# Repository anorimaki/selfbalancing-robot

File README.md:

# SelfBalancing Robot (Yes, another self balancing robot...)

Self balanced robot that exposes a REST API to control it.

The Web is plenty of self balancing robots, vehicles with two wheels perpendiculars to the direction of movement that keep the equilibrium. This is just another one with WiFi connection.

## Features
- The robot keeps balanced :)
- REST API for: (documented [here](firmware/esp8266/doc/restapi.md))
  - Setting control algorithms parameters.
  - Getting runtime control data.
  - Setting speed and heading.

## Respository contents
- [`client/android`](client/android): Simple Android application to control robot movements via the REST API.
- [`client/htlm`](client/html): Single page Web application that renders runtime PID algorithm data. It also allows for getting and setting robot control parameters.
- [`client/testserver`](client/testserver): Robot REST API emulator for client development purposes.
- [`firmware/esp8266`](firmware/esp8266): Firmware source for ESP8266 controller.
- [`firmware/pic`](firmware/pic): Firmware source for PIC24FJ32GA002 controller.
- [`schematics`](schematics): Electronics schematics for [KiCad](http://kicad-pcb.org) suite.

## How it works
The robot [chassis](doc/chassis.md) consists of a platform with two DC motors and its wheels that form an [inverted pendulum](https://en.wikipedia.org/wiki/Inverted_pendulum). A circuit board monitors the inclination of the robot (pitch) and drives motors to keep the robot in balance.

The circuit has three main components:
- **[MPU-9250](https://www.invensense.com/wp-content/uploads/2015/02/PS-MPU-9250A-01-v1.1.pdf)**: It is a single chip that contains a 3-axis gyroscope, a 3-axis accelerometer and a compass. It runs a fusion algorithm for gyroscope and accelerometer outputs called Digital Motion 
Processor (DMP) that frees the PIC microcontroller of doing this work (compass is not used in this project). DMP outputs [quaternions](https://en.wikipedia.org/wiki/Quaternion) that are converted to pitch angles by PIC24FJ32GA002. MPU-9250 is assembled on a breakout board.

- **[PIC24FJ32GA002](https://www.microchip.com/wwwproducts/en/PIC24FJ32GA002)**: It is a 16-bit microcontroller that:
  - Calculates current pitch from MPU-9250 quaternions output.
  - Gets current speed and calculates heading based on motors encoders output.
  - Implements control algorithms for balancing, speed and heading.
  - Sets motors power.

- **[ESP8266](https://en.wikipedia.org/wiki/ESP8266)**: It is a cheap 32-bit microcontroller with WiFi connection that is assembled on a ESP12F breakout board. In this project, ESP8266:
  - Serves a REST API that enables clients to communicate with the robot.
  - Resolves REST API requests communicating with PIC24FJ32GA002 via I2C.
  - Initializes MPU-9250 module to save program memory space in the PIC24FJ32GA002. The MPU-9250 initialization requires loading the compiled DMP  firmware each time it is powered up. Therefore, this firmware should be stored in the PIC program memory reducing its capacity by 20%. In ESP8266 this is not a problem because ESP12F has 4MB of flash.

## Software Build
Build instructions for the two firmware code and REST client examples can be found in its own directory.

## Acknowledges
- To hobbits that share their projects and knowledge in GitHub, StackOverflow, StackExchange, Wikipedia, electronics forums...
- To previous hosts that permit people to share their knowledge.

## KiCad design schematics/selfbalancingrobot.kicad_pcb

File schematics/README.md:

# SelfBalancing Robot: schematics
This directory contains schematics for [KiCad](http://kicad-pcb.org) suite.

## Connectors, Buttons and LED locations

## Improvements

### Power rail generation
There are two lineal regulators to generate power rails, a 7805 and a LM1117-3.3. The 7805 is connected to the battery which can not be the same battery used for the motors because too much power would be dissipated in the regulator. The motors need a 12V battery and the circuit consumes about 250mA, so it would be about 1.75W! With a dedicated 7.4V battery, the power dissipation is reduced but remains too high (about 600mW). 

A buck converter to generate the 5V power rail would have been a better choice because it would be more efficient (extending battery life) and eliminate the need of a second battery (the circuit could be plugged with the 12V battery).

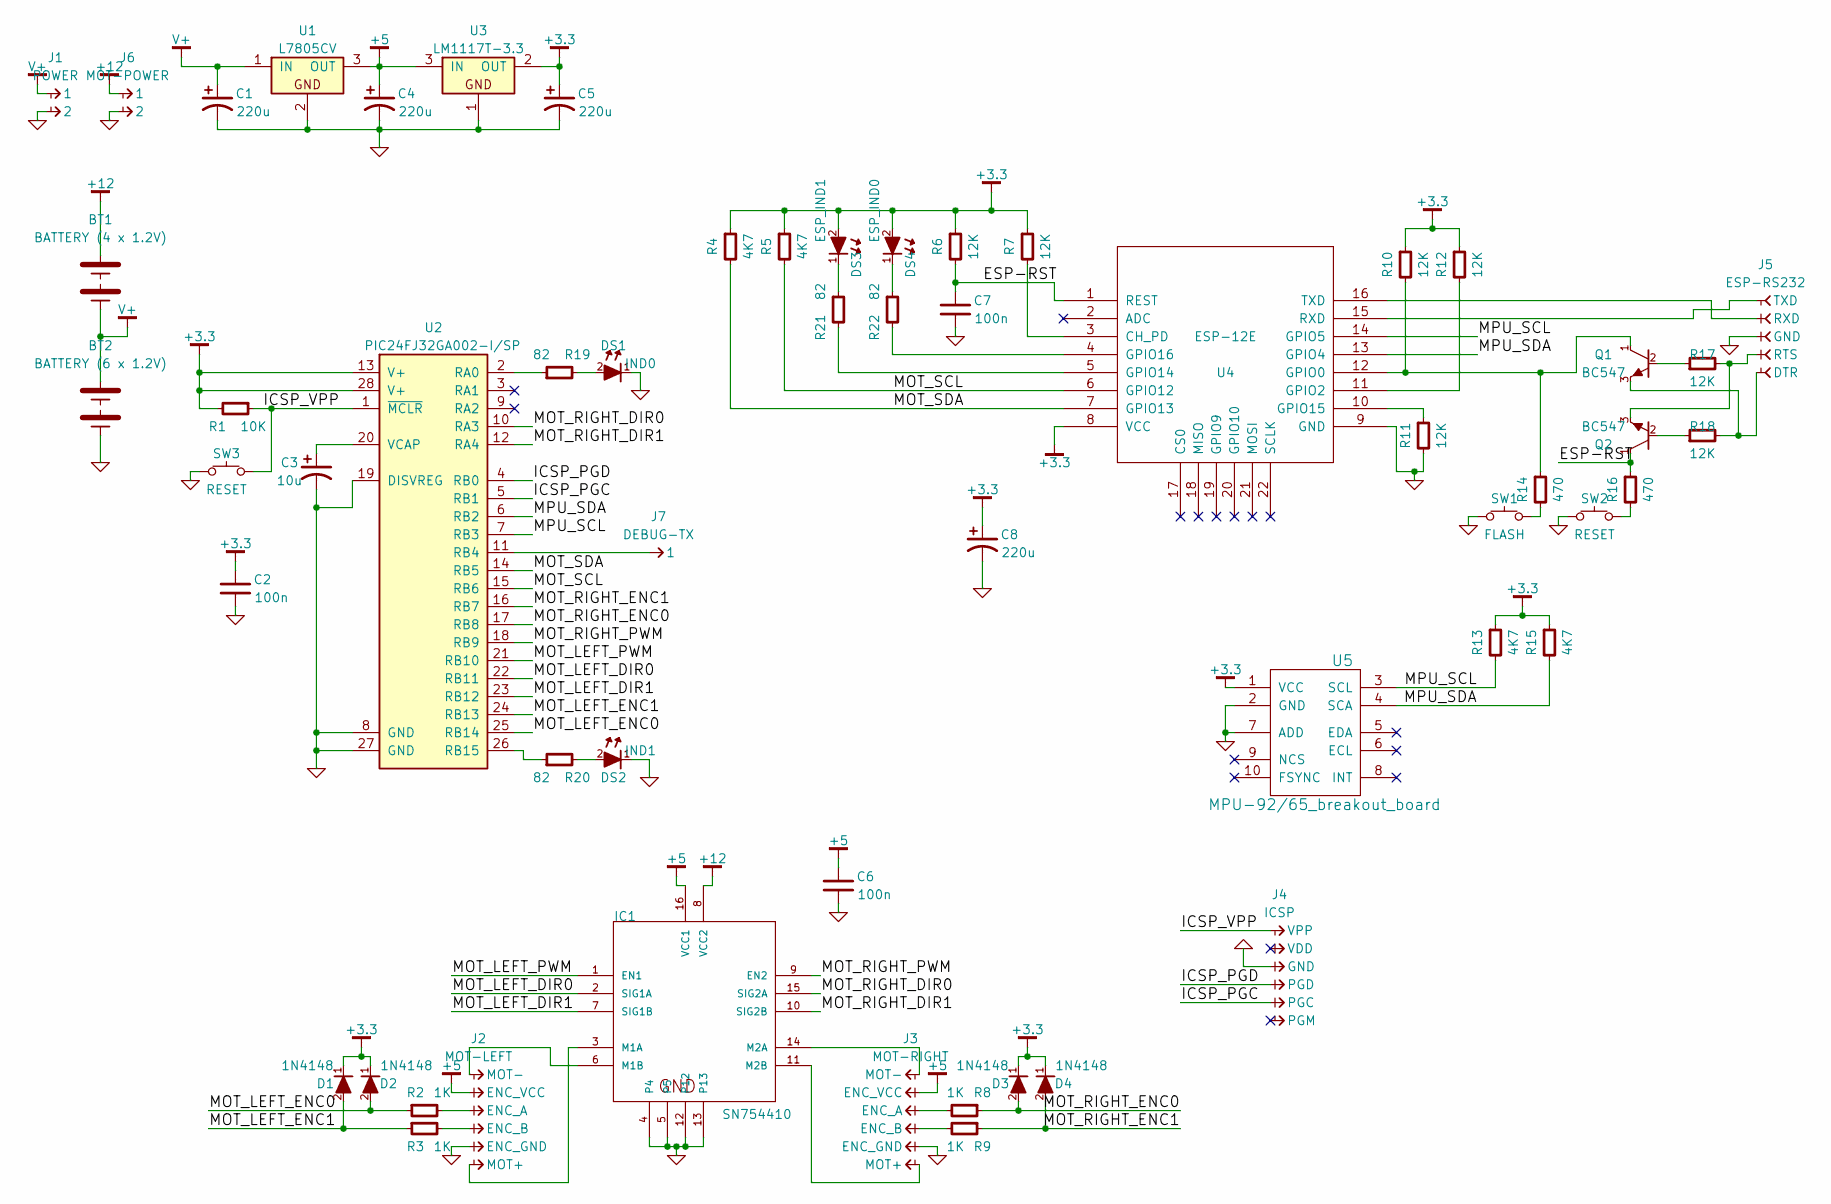
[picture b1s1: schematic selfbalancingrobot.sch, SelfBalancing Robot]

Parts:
BT1: BATTERY (4 x 1.2V)
BT2: BATTERY (6 x 1.2V)
C1, C4, C5, C8: 220u; C-ALUM-8mm
C2, C6, C7: 100n; C-FILM-2.5mm
C3: 10u; C-ALUM-5mm
D1, D2, D3, D4: 1N4148; DO-35
DS1: IND0; LED-3mm
DS2: IND1; LED-3mm
DS3: ESP_IND1; LED-3mm
DS4: ESP_IND0; LED-3mm
IC1: SN754410; DIP-16
J1: POWER; CONN-100MIL-M-1x2-SHROUD
J2: MOT-LEFT; CONN-100MIL-M-1x6-SHROUD
J3: MOT-RIGHT; CONN-100MIL-M-1x6-SHROUD
J4: ICSP; CONN-100MIL-M-1x6-SHROUD
J5: ESP-RS232; CONN-100MIL-F-1x5
J6: MOT-POWER; CONN-100MIL-M-1x2-SHROUD
J7: DEBUG-TX; CONN-100MIL-M-1x1
Q1, Q2: BC547; TO-92
R1: 10K; R-250mW
R2, R3, R8, R9: 1K; R-250mW
R4, R5, R13, R15: 4K7; R-250mW
R6, R7, R10, R11, R12, R17, R18: 12K; R-250mW
R14, R16: 470; R-250mW
R19, R20, R21, R22: 82; R-250mW
SW1: FLASH; SW_PUSH_6mm_h5mm
SW2, SW3: RESET; SW_PUSH_6mm_h5mm
U1: L7805CV; TO-220; MPN L78{vout}CV
U2: PIC24FJ32GA002-I/SP; DIP-28; MPN PIC24FJ32GA002-I/SP
U3: LM1117T-3.3; TO-220; MPN LM1117T-{vout}
U4: ESP-12E; ESP-12
U5: MPU-92/65_breakout_board; MPU9265_breakout

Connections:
+3.3: C2.1, C5.1, C8.1, D1.1 (K), D2.1 (K), D3.1 (K), D4.1 (K), DS3.2 (A), DS4.2 (A), R1.2, R4.1, R5.1, R6.1, R7.1, R10.1, R12.1, R13.1, R15.1, U2.13 (V+), U2.28 (V+), U3.2 (OUT), U4.8 (VCC), U5.1 (VCC); also elsewhere on the board
+5: C4.1, C6.1, IC1.16 (VCC1), J2.2 (ENC_VCC), J3.2 (ENC_VCC), U1.3 (OUT), U3.3 (IN)
+12: BT1.1 (+), IC1.8 (VCC2), J6.1
/ESP-RST: C7.1, Q2.1 (C), R6.2, R16.1, U4.1 (REST)
/ICSP_PGC: J4.5 (PGC), U2.5 (RB1)
/ICSP_PGD: J4.4 (PGD), U2.4 (RB0)
/ICSP_VPP: J4.1 (VPP), R1.1, SW3.2, U2.1 (~MCLR)
/MOT_LEFT_DIR0: IC1.2 (SIG1A), U2.22 (RB11)
/MOT_LEFT_DIR1: IC1.7 (SIG1B), U2.23 (RB12)
/MOT_LEFT_ENC0: D2.2 (A), R2.1, U2.25 (RB14)
/MOT_LEFT_ENC1: D1.2 (A), R3.1, U2.24 (RB13)
/MOT_LEFT_PWM: IC1.1 (EN1), U2.21 (RB10)
/MOT_RIGHT_DIR0: IC1.15 (SIG2A), U2.10 (RA3)
/MOT_RIGHT_DIR1: IC1.10 (SIG2B), U2.12 (RA4)
/MOT_RIGHT_ENC0: D3.2 (A), R8.1, U2.17 (RB8)
/MOT_RIGHT_ENC1: D4.2 (A), R9.1, U2.16 (RB7)
/MOT_RIGHT_PWM: IC1.9 (EN2), U2.18 (RB9)
/MOT_SCL: R5.2, U2.15 (RB6), U4.6 (GPIO12)
/MOT_SDA: R4.2, U2.14 (RB5), U4.7 (GPIO13)
/MPU_SCL: R13.2, U2.7 (RB3), U4.14 (GPIO5), U5.3 (SCL)
/MPU_SDA: R15.2, U2.6 (RB2), U4.13 (GPIO4), U5.4 (SCA)
GND: BT2.2 (-), C1.2, C2.2, C3.2, C4.2, C5.2, C6.2, C7.2, C8.2, DS1.1 (K), DS2.1 (K), IC1.4, IC1.5, IC1.12, IC1.13, J1.2, J2.5 (ENC_GND), J3.5 (ENC_GND), J4.3 (GND), J5.3 (GND), J6.2, R11.2, SW1.1, SW2.1, SW3.1, U1.2, U2.8 (GND), U2.19 (DISVREG), U2.27 (GND), U3.1, U4.9 (GND), U5.2 (GND), U5.7 (ADD)
unnamed: C3.1, U2.20 (VCAP)
unnamed: DS1.2 (A), R19.2
unnamed: DS2.2 (A), R20.2
unnamed: DS3.1 (K), R21.1
unnamed: DS4.1 (K), R22.1
unnamed: IC1.3 (M1A), J2.6 (MOT+)
unnamed: IC1.6 (M1B), J2.1 (MOT-)
unnamed: IC1.11 (M2B), J3.6 (MOT+)
unnamed: IC1.14 (M2A), J3.1 (MOT-)
unnamed: J2.3 (ENC_A), R2.2
unnamed: J2.4 (ENC_B), R3.2
unnamed: J3.3 (ENC_A), R8.2
unnamed: J3.4 (ENC_B), R9.2
unnamed: J5.1 (TXD), U4.15 (RXD)
unnamed: J5.2 (RXD), U4.16 (TXD)
unnamed: J5.4 (RTS), Q2.3 (E), R17.2
unnamed: J5.5 (DTR), Q1.3 (E), R18.2
unnamed: J7.1, U2.11 (RB4)
unnamed: Q1.1 (C), R10.2, R14.1, U4.12 (GPIO0)
unnamed: Q1.2 (B), R17.1
unnamed: Q2.2 (B), R18.1
unnamed: R7.2, U4.3 (CH_PD)
unnamed: R11.1, U4.10 (GPIO15)
unnamed: R12.2, U4.11 (GPIO2)
unnamed: R14.2, SW1.2
unnamed: R16.2, SW2.2
unnamed: R19.1, U2.2 (RA0)
unnamed: R20.1, U2.26 (RB15)
unnamed: R21.2, U4.5 (GPIO14)
unnamed: R22.2, U4.4 (GPIO16)
V+: BT1.2 (-), BT2.1 (+), C1.1, J1.1, U1.1 (IN)

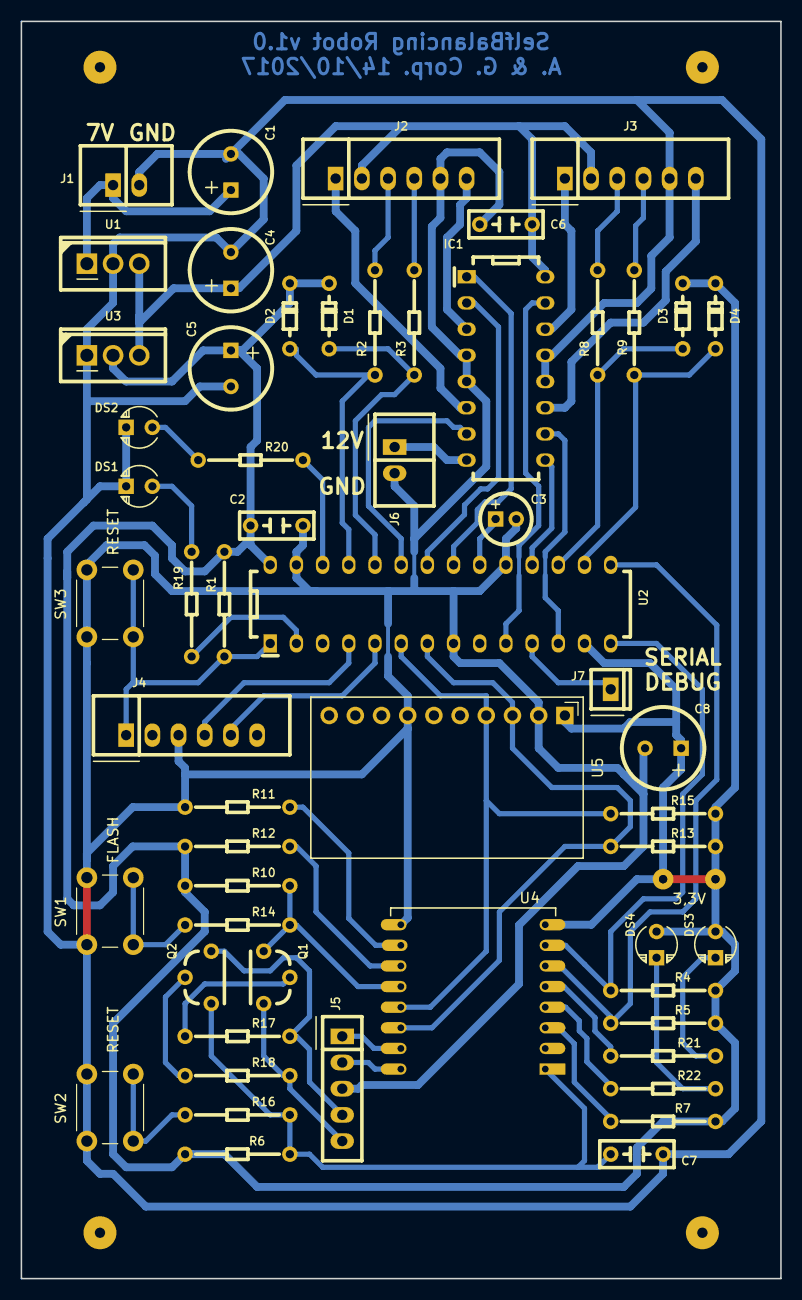
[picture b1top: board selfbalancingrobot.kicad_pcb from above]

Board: 2 copper layers, 73.7 x 121.9 mm, 57 parts (0 on the bottom side), 53 nets.

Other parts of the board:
3,3V: SolderWirePad_single_0-8mmDrill

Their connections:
+3.3: 3,3V.1; also elsewhere on the board

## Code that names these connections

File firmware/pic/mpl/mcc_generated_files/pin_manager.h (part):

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*/
/**
  @Summary
    Sets the GPIO pin, RA0, high using LATA0.

  @Description
    Sets the GPIO pin, RA0, high using LATA0.

  @Preconditions
    The RA0 must be set to an output.
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#define led0_SetHigh()          _LATA0 = 1
/**
  @Summary
    Sets the GPIO pin, RA0, low using LATA0.

  @Description
    Sets the GPIO pin, RA0, low using LATA0.

  @Preconditions
    The RA0 must be set to an output.
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#define led0_SetLow()           _LATA0 = 0
/**
  @Summary
    Toggles the GPIO pin, RA0, using LATA0.

  @Description
    Toggles the GPIO pin, RA0, using LATA0.

  @Preconditions
    The RA0 must be set to an output.
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#define led0_Toggle()           _LATA0 ^= 1
/**
  @Summary
    Reads the value of the GPIO pin, RA0.

  @Description
    Reads the value of the GPIO pin, RA0.

  @Preconditions
    None.
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    </code>

*/
#define led0_GetValue()         _RA0
/**
  @Summary
    Configures the GPIO pin, RA0, as an input.

  @Description
    Configures the GPIO pin, RA0, as an input.

  @Preconditions
    None.
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#define led0_SetDigitalInput()  _TRISA0 = 1
/**
  @Summary
    Configures the GPIO pin, RA0, as an output.

  @Description
    Configures the GPIO pin, RA0, as an output.

  @Preconditions
    None.
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#define led0_SetDigitalOutput() _TRISA0 = 0
/**
  @Summary
    Sets the GPIO pin, RA3, high using LATA3.

  @Description
    Sets the GPIO pin, RA3, high using LATA3.

  @Preconditions
    The RA3 must be set to an output.
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#define motors_right_dir0_SetHigh()          _LATA3 = 1
/**
  @Summary
    Sets the GPIO pin, RA3, low using LATA3.

  @Description
    Sets the GPIO pin, RA3, low using LATA3.

  @Preconditions
    The RA3 must be set to an output.
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#define motors_right_dir0_SetLow()           _LATA3 = 0
/**
  @Summary
    Toggles the GPIO pin, RA3, using LATA3.

  @Description
    Toggles the GPIO pin, RA3, using LATA3.

  @Preconditions
    The RA3 must be set to an output.
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#define motors_right_dir0_Toggle()           _LATA3 ^= 1
/**
  @Summary
    Reads the value of the GPIO pin, RA3.

  @Description
    Reads the value of the GPIO pin, RA3.

  @Preconditions
    None.
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    </code>

*/
#define motors_right_dir0_GetValue()         _RA3
/**
  @Summary
    Configures the GPIO pin, RA3, as an input.

  @Description
    Configures the GPIO pin, RA3, as an input.

  @Preconditions
    None.
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#define motors_right_dir0_SetDigitalInput()  _TRISA3 = 1
/**
  @Summary
    Configures the GPIO pin, RA3, as an output.

  @Description
    Configures the GPIO pin, RA3, as an output.

  @Preconditions
    None.
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#define motors_right_dir0_SetDigitalOutput() _TRISA3 = 0
/**
  @Summary
    Sets the GPIO pin, RA4, high using LATA4.

  @Description
    Sets the GPIO pin, RA4, high using LATA4.

  @Preconditions
    The RA4 must be set to an output.
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#define motors_right_dir1_SetHigh()          _LATA4 = 1
/**
  @Summary
    Sets the GPIO pin, RA4, low using LATA4.

  @Description
    Sets the GPIO pin, RA4, low using LATA4.

  @Preconditions
    The RA4 must be set to an output.
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#define motors_right_dir1_SetLow()           _LATA4 = 0
/**
  @Summary
    Toggles the GPIO pin, RA4, using LATA4.

  @Description
    Toggles the GPIO pin, RA4, using LATA4.

  @Preconditions
    The RA4 must be set to an output.
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#define motors_right_dir1_Toggle()           _LATA4 ^= 1
/**
  @Summary
    Reads the value of the GPIO pin, RA4.

  @Description
    Reads the value of the GPIO pin, RA4.

  @Preconditions
    None.
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    </code>

*/
#define motors_right_dir1_GetValue()         _RA4
/**
  @Summary
    Configures the GPIO pin, RA4, as an input.

  @Description
    Configures the GPIO pin, RA4, as an input.

  @Preconditions
    None.
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#define motors_right_dir1_SetDigitalInput()  _TRISA4 = 1
/**
  @Summary
    Configures the GPIO pin, RA4, as an output.

  @Description
    Configures the GPIO pin, RA4, as an output.

  @Preconditions
    None.
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#define motors_right_dir1_SetDigitalOutput() _TRISA4 = 0
/**
  @Summary
    Sets the GPIO pin, RB11, high using LATB11.

  @Description
    Sets the GPIO pin, RB11, high using LATB11.

  @Preconditions
    The RB11 must be set to an output.
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#define motors_left_dir0_SetHigh()          _LATB11 = 1
/**
  @Summary
    Sets the GPIO pin, RB11, low using LATB11.

  @Description
    Sets the GPIO pin, RB11, low using LATB11.

  @Preconditions
    The RB11 must be set to an output.
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#define motors_left_dir0_SetLow()           _LATB11 = 0
/**
  @Summary
    Toggles the GPIO pin, RB11, using LATB11.

  @Description
    Toggles the GPIO pin, RB11, using LATB11.

  @Preconditions
    The RB11 must be set to an output.
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#define motors_left_dir0_Toggle()           _LATB11 ^= 1
/**
  @Summary
    Reads the value of the GPIO pin, RB11.

  @Description
    Reads the value of the GPIO pin, RB11.

  @Preconditions
    None.
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    </code>

*/
#define motors_left_dir0_GetValue()         _RB11
/**
  @Summary
    Configures the GPIO pin, RB11, as an input.

  @Description
    Configures the GPIO pin, RB11, as an input.

  @Preconditions
    None.
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#define motors_left_dir0_SetDigitalInput()  _TRISB11 = 1
/**
  @Summary
    Configures the GPIO pin, RB11, as an output.

  @Description
    Configures the GPIO pin, RB11, as an output.

  @Preconditions
    None.
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#define motors_left_dir0_SetDigitalOutput() _TRISB11 = 0
/**
  @Summary
    Sets the GPIO pin, RB12, high using LATB12.

  @Description
    Sets the GPIO pin, RB12, high using LATB12.

  @Preconditions
    The RB12 must be set to an output.
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#define motors_left_dir1_SetHigh()          _LATB12 = 1
/**
  @Summary
    Sets the GPIO pin, RB12, low using LATB12.

  @Description
    Sets the GPIO pin, RB12, low using LATB12.

  @Preconditions
    The RB12 must be set to an output.
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#define motors_left_dir1_SetLow()           _LATB12 = 0
/**
  @Summary
    Toggles the GPIO pin, RB12, using LATB12.

  @Description
    Toggles the GPIO pin, RB12, using LATB12.

  @Preconditions
    The RB12 must be set to an output.
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#define motors_left_dir1_Toggle()           _LATB12 ^= 1
/**
  @Summary
    Reads the value of the GPIO pin, RB12.

  @Description
    Reads the value of the GPIO pin, RB12.

  @Preconditions
    None.
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    </code>

*/
#define motors_left_dir1_GetValue()         _RB12
/**
  @Summary
    Configures the GPIO pin, RB12, as an input.

  @Description
    Configures the GPIO pin, RB12, as an input.

  @Preconditions
    None.
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#define motors_left_dir1_SetDigitalInput()  _TRISB12 = 1
/**
  @Summary
    Configures the GPIO pin, RB12, as an output.

  @Description
    Configures the GPIO pin, RB12, as an output.

  @Preconditions
    None.
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#define motors_left_dir1_SetDigitalOutput() _TRISB12 = 0
/**
  @Summary
    Sets the GPIO pin, RB13, high using LATB13.

  @Description
    Sets the GPIO pin, RB13, high using LATB13.

  @Preconditions
    The RB13 must be set to an output.
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#define motors_left_qenc1_SetHigh()          _LATB13 = 1
/**
  @Summary
    Sets the GPIO pin, RB13, low using LATB13.

  @Description
    Sets the GPIO pin, RB13, low using LATB13.

  @Preconditions
    The RB13 must be set to an output.
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#define motors_left_qenc1_SetLow()           _LATB13 = 0
/**
  @Summary
    Toggles the GPIO pin, RB13, using LATB13.

  @Description
    Toggles the GPIO pin, RB13, using LATB13.

  @Preconditions
    The RB13 must be set to an output.
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#define motors_left_qenc1_Toggle()           _LATB13 ^= 1
/**
  @Summary
    Reads the value of the GPIO pin, RB13.

  @Description
    Reads the value of the GPIO pin, RB13.

  @Preconditions
    None.
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    </code>

*/
#define motors_left_qenc1_GetValue()         _RB13
/**
  @Summary
    Configures the GPIO pin, RB13, as an input.

  @Description
    Configures the GPIO pin, RB13, as an input.

  @Preconditions
    None.
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#define motors_left_qenc1_SetDigitalInput()  _TRISB13 = 1
/**
  @Summary
    Configures the GPIO pin, RB13, as an output.

  @Description
    Configures the GPIO pin, RB13, as an output.

  @Preconditions
    None.
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#define motors_left_qenc1_SetDigitalOutput() _TRISB13 = 0
/**
  @Summary
    Sets the GPIO pin, RB14, high using LATB14.

  @Description
    Sets the GPIO pin, RB14, high using LATB14.

  @Preconditions
    The RB14 must be set to an output.
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#define motors_left_qenc0_SetHigh()          _LATB14 = 1
/**
  @Summary
    Sets the GPIO pin, RB14, low using LATB14.

  @Description
    Sets the GPIO pin, RB14, low using LATB14.

  @Preconditions
    The RB14 must be set to an output.
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#define motors_left_qenc0_SetLow()           _LATB14 = 0
/**
  @Summary
    Toggles the GPIO pin, RB14, using LATB14.

  @Description
    Toggles the GPIO pin, RB14, using LATB14.

  @Preconditions
    The RB14 must be set to an output.
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#define motors_left_qenc0_Toggle()           _LATB14 ^= 1
/**
  @Summary
    Reads the value of the GPIO pin, RB14.

  @Description
    Reads the value of the GPIO pin, RB14.

  @Preconditions
    None.
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    </code>

*/
#define motors_left_qenc0_GetValue()         _RB14
/**
  @Summary
    Configures the GPIO pin, RB14, as an input.

  @Description
    Configures the GPIO pin, RB14, as an input.
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
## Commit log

2017-02-10 - Commit inicial. Pruebas con mpu9250
2017-02-23 Pruebas con el mpu9250
2017-02-28 - Pruebas con mpu9250:
    - Se calculan los ángulos correctamente
2017-03-09 Pruebas con esp8266: Empezado intento de integración con mpu9250.
2017-03-12 Pruebas con esp8266:
    Integración con mpu9250 y servidor http (hello world) funcionando
2017-03-28 - Cambiado de compilador de CCS a XC16 para el PIC24F
2017-03-30 - Añadidos ficheros de configuración de los perifericos del PIC24 (MPLAB Code Configurator)
2017-03-30 - Empezada a pasar inicialización del MPU al esp8266
2017-04-09 - Ampliada la librería MPU en el esp8266
    - Corregidos errores de porting de driver original esp8266:
    - Logs de floats
    - Código de error en mpu_init según fallo.
    - Transladada la carga del firmware del DMP al esp8266 (Ya es funcional):
    - Micro motores: Cambiada función mpu_init del driver original para que no haga ninguna acción y solo establezca el estado del propio driver según la inicialización hecha en el esp8266.
    - Coregidos errores en el adaptador del driver del MPU.
2017-04-13 PIC motores:
    - Añadido control por PWM para los motores.
    - Añadido PID (sólo con constante proporcional)
    - Cambiado I2C1 a pines principales (para intenrtar solucionar el problema de comunicación)
    - Corregido fix16_to_str para números negativos.
2017-04-24 Micro motores:
    - Añadida librería de preprocesador de la boost.
    - I2C1 en los PINs alternativos.
    - Camabiada salida de RA1 a RA4. El puerto RA1 ha subrido un percance y está en coto con VDD. Recuperaremos RA1 cuando tenga PICs nuevos.
    - Mejoras en la integración del algoritmo PID con los motores.
2017-05-11 - Empezado cliente HTML para control del robot.
    - esp8266
    - Añadido endpoint /motors/pitch/state (no probado)
    - Centralizada la implementación de comunicación I2C con el PIC.
    - PIC motores:
    - Añadida interrupción por cambio de estado en
2017-05-19 - Cliente HTML para control del robot:
    - Añadido gráfico pitch
2017-06-10 - Cliente HTML:
    - Uso de graficos devextreme encapsulado en componente propio.
    - esp8266
    - Inicialización movida al Application::init()
    - Mejorado rendimiento de la transmisión WiFi con buffer de 1760 y setNoDelay(1)
    - Adaptado a protocolo de recibir/enviar un array de estados para el pitch.
    - pic (motor controller)
2017-06-17 - pic (motor controller)
    - Corregido pid_init (no se establecía el valor máximo del store) y pid_compute (no se incrmentaba el tamaño del store)
2017-06-28 - Cliente HTML:
    - Cambiada librería de gráfico por amChart
    - Introducido @angular/flex-layout
    - Introducido @angular/material
    - esp8266
    - Cambiado mensaje de estado de PID para reducir el tamaño
    - pic (motor controller)
2017-07-01 - Cliente HTML:
    - Refactorización para seguir las convencions de Angular2.
2017-07-02 - Cliente HTML:
    - Correcciones menores
2017-07-04 - Añadido protocolo para leer y establecer los PIDSettings de pith entre cliente y esp8266
2017-07-23 Cliente Html:
    - Multiples categorias para los gráficos (ahora salen escalados)
    - Otras mejoras.
    esp8266:
    - Añadida calibración del MPU en el inicio.
    - Eliminada la brújula en el test del MPU. Siempre daba errores.
    PIC motores:
2017-07-29 Clente HTML:
    - Corregido algoritmo PID según el controlador de los motores (PIC)
    - Eliminada leyenda adicional. Se usa la que proporciona amCharts.
    - Limitado el número de puntos a 1000 para evitar problemas de rendimiento.
    Servidor RETS (esp8266):
    - Añadido tratamiento de cambeceras Access-Control-Request-Headers y Access-Control-Request-Method para soportar CORS.
    Control de motores (PIC)
2017-10-10 - Añadido esquemático y PCB
    - Reasignación de PINs de los microcontroladores para facilitar elenrutado del PCB
2017-10-12 - Refinado PCB
2017-10-12 - Eliminados submodulos GIT
2017-10-12 Añadido archivo con dos PCB para impresión
2017-11-01 - Mejorada señalización por leds en PIC y ESP8266
    - ESP8266: Un error de la conexión a la Wifi permite continuar el programa
2017-11-01 - Actualizadas versiones de las dependencias del cliente angular2
2017-11-23 - Refactorización del cliente HTML.
    - Empezado a introducir el control de velocidad en el PIC
    - Conversión de nivel de potencia a PWD de los motores más proporcional.
2017-11-25 - Cliente HTML
    - Cambiado amCharts port Canvasjs.
2017-12-02 Cliente HTML:
    - Añadido gráfico de velocidad.
    esp8266/PIC:
    - Añadido endpoint REST para obtener los datos de velocidad.
2017-12-10 Cliente HTML:
    - script canvas.min.js local.
    - Pitch: Eje X mostrado en segundos.
    - Pitch: Valor current mostrado en grados.
    - Eliminadas referencias a AmCharts.
    - Actualizadas versiones de librerías de terceros (angular 5, ...)
    esp8266:
2017-12-17 - PIC
    - Ajustado valor mínimo del PWM para los motores.
    - Corregido el PID store para que no devolver una entrada a medio escribir en el caso que el write_ptr alcanzase al read_ptr.
    - Añadido indicador para errores en el MPU durante el ciclo normal.
    - Aumentada la frecuencia de ejecución del PID de pitch a 200Hz.
    - ESP:
    - Cambiado tipo buffer para construcción del JSON a estático.
2017-12-28 - Añadida calibración del MPU desde la interfaz HTML.
    - Añadido target en el gráfico del PID en la interfaz HTML.
    - Cambiada función del botón del ESP8266. Ahora permite ajustar el offset del pitch en el PIC en vez de calibrar el MPU.
2018-01-28 * Intefaz HTML
    - Corregido bug en el cambio de vistas de datos. Los datos se estaban adaptando en cada visualización.
    * Cambiadas constantes PID de signed a unsigned.
    * PIC:
    - Actualizada versión del compilador.
    - PID: Aumentado el rango del valor de integración para que tenga una mayor influencia cuando la desviación en el tiempo persista.
    - Habitilado el control de velocidad para que calcule el pitch objetivo.
2018-02-01 - Empezado cliente Android
2018-02-05 Cliente HTML:
    - Añadido control de heading
    - Corregido ajustes de valores en PitchStep
    - Corregido ajustes de valores en PitchStep
    ESP8266:
    - Añadida API REST para control de heading
    - Añadido enpoint para establecer los targets de speed y heading
2018-02-05 - Correcciones en el cliente Android. - Añadido al servidor de test los endpoints para estblacer los targets de velocidad y heading
2018-02-09 - Continuada evolución del clietne Android.
    - ESP8266:
    Corregido bug en el set de los targets.
    - PIC:
    Corregido bug en el i2c del PID del heading
    Bajado elperiodo de control de velocidad a 50ms
2018-02-12 Cliente Android:
    Ajustados valores enviados al rango de bits del PID.
    Clietne HTML:
    Añadidos settings del heading
    ESP8266
    Añadida traza de errores para obtener mejor información e los clintes cuando se produce un 500.
    PIC:
2018-02-12 Cliente android: - Añadido Dagger. - Añadida visualización de tiempo de respuesta.
2018-02-24 - Cliente HTML:
    - Corregida constante PID_MIN_INTEGRAL_ERROR
    - La obtención de datos de los diferentes PIDs se puede habilitar/deshabilitar individualmente.
    - ESP8266:
    - Soporte para compilación desde línea de comandos:
    - Añadido makefile
    - Añadida librería ArduinoJson
2018-02-24 - Añadido PDF de los esquemáticos
2018-03-03 - Directorios esp8266 y piccode movidos a firmaware/esp8266 y firmaware/pic
    - ESP8266:
    - Adaptado a versión de Arduino Core for ESP8266 2.4.0.
    - Es necesrio poner la cabecera 'Access-Control-Allow-Origin' explícitamente ya que la nueva versión de ESP8266WebServer ya no la pone por defecto.
    - PIC:
    - Rebajado valor máximo de error integral en el controlador PID a 0x3FFF
    - Rebajado el periodo de ejecución del controlador de velodidad y cabeceo a 50ms.
2018-03-07 - Empezado a añadir READMEs
2018-03-11 - Cliente Android:
    - Añadida posibilidad de configurar la IP (aunque hay que reiniciar la app para que tenga efecto)
    - Cliente Angular:
    - Actualizadas dependencias
    - Limpieza en el código según tslint
    - ESP8266
    - Soporte para conexión como AP
2018-03-18 - ESP8266: Migración a servidor Web asíncrono (AsyncWebServer)
2018-03-18 - ESP8266:
    - Cambiado endpoint de obtención de estado del PID para reducir memoria.
    - Añadida actualziación por OTA.
2018-03-22 - ESP8266:
    - Deshabilitado algoritmo de Nagle para ver si mejoraba la velocidad con más de dos conexiones. No se aprecia mejora.
    - Liberada RAM: Cadenas de texto y firmware del MPU pasadas a la memoria flash
    - Cliente Angular:
    - Corregida construcciónde la URL para entorno de producción.
2018-03-24 - ESP8266:
    - Añadidas librerías de thrid-parties
    - Mejorado el consumo de RAM:
    - Implementación especifica AsyncNoTemplateStreamResponse para la gestionar la respuesta a los estados de los PID.
    - Limitado el número de estados PID que se reciben del PIC.
2018-03-24 - PIC:
    - Cambiada velocidad del I2C de comunicación con el MPU a 400KH
    - Cliente HTML:
    - Reemplazada clase obsoleta Http de Angular por la HttpClient.
    - Corregido error en el RbChartComponent
2018-03-26 - Empezada interfaz para gestionar la conexión WiFi
    - Cliente Angular:
    - Movido el portal actual al subportal 'robot'
    - Creada estructura para el subportal 'wifi'
    - Añadida carga diferida de módulos
    - ESP8266:
    - Añadido soporte para el routing de Angular (devolver el index.html ante las rutas de angular)
2018-04-06 - Mejora de la documentación
2018-04-08 - Continuada consola WiFi
2018-04-08 - Cambiado cliente Angular para refrescar la información del modo station cada segundo.
2018-04-13 - Portal WiFi: Añadido scan de APs
2018-04-13 - ESP8266: Añadido scan de APs
2018-04-13 - Portal WiFi: Cambio menor
2018-04-21 - PIC:
    - Aumentado el periodo de ejecución del control de velidad a 200ms
    - Aumentado valor máximo de error integral a 2^16
2018-04-21 Android:
    - Soporte para SDK-API 16
    PIC: Acabados de ajustar parámetros del PID.
2018-05-03 - Corregido script de compilación para esp8266 en linux.
    - Añadido travis para firmware esp8266
2018-05-03 Prueba de Travis-CI
2018-05-03 - Añadidos permisos de ejecución a los wrappers de gradle
2018-05-04 - Añadido build de la consola HTML al Travis.
2018-05-04 - Añadidas traducciones de los strings de la aplicación Android.
2018-05-04 - Intento de corrección del script de Travis-CI.
2018-05-04 - Cliente HTML
    - Actualizado Angular 6 y rxjs 6

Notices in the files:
firmware/pic/mpl/mcc_generated_files/pin_manager.h:
Copyright (c) 2013 - 2015 released Microchip Technology Inc.  All rights reserved.
